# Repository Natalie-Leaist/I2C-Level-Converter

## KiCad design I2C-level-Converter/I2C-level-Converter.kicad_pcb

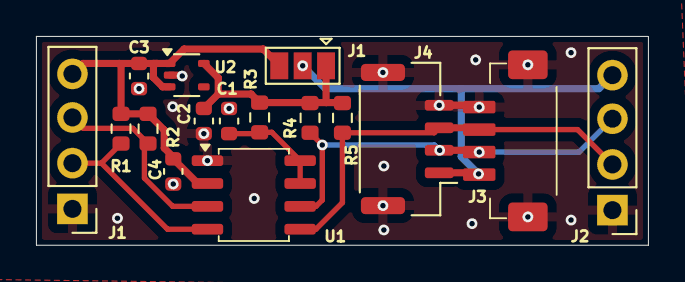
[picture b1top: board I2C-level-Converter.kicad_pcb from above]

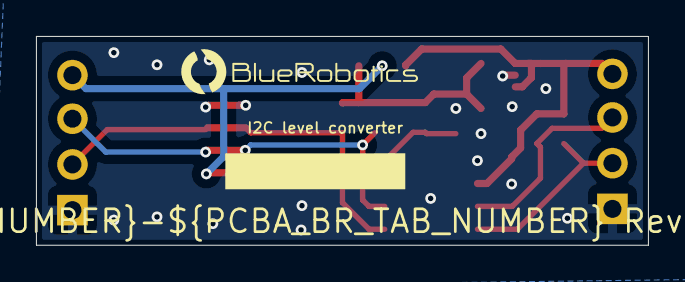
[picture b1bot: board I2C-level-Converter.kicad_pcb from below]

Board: 2 copper layers, 34.0 x 11.6 mm, 18 parts (2 on the bottom side), 9 nets.

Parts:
C1, C4: 100nF 100V; C_0603_1608Metric-minimized
C2, C3: 1uF 50V; C_0603_1608Metric-minimized
GL1: JLC_Number
GL2: BR_Logo
J1: Pin_Header_1x4_2.54mm_Vertical
J1#2: Solder_Jumper_3_Bridged12_flipped; SolderJumper-3_P1.3mm_Open_Pad1.0x1.5mm_paste
J2: 4-pin header; Pin_Header_1x4_2.54mm_Vertical
J3: DF13-4P-1.25V(21); HRS_DF13C_4P_1.25V(21)
J4: 4-pin GH; BM04B-GHS-TBT
R1, R2, R4, R5: 1k; R_0603_1608Metric
R3: 200k; R_0603_1608Metric
U1: PCA9306D,118; SO-8_3.9x4.9mm_P1.27mm_correct
U2: MIC5365-3.3YC5; SOT-353_SC-70-5

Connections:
3.3V: C2.1, J1#2.1 (B), R3.1, R4.1, R5.1, U2.5 (VOUT)
5V: C3.1, C4.1, J1.4, J1#2.3 (A), R1.1, R2.1, U1.2 (VREF1), U2.1 (VIN), U2.3 (EN)
/SCL1: J1.3, R2.2, U1.3 (SCL1)
/SCL2: J2.3, J3.2 (Pin_A2), J4.2, R4.2, U1.6 (SCL2)
/SDA1: J1.2, R1.2, U1.4 (SDA1)
/SDA2: J2.2, J3.3 (Pin_A3), J4.3, R5.2, U1.5 (SDA2)
GND: C1.2, C2.2, C3.2, C4.2, J1.1, J2.1, J3.4 (Pin_A4), J3.MP, J4.4, J4.MP, U1.1 (GND), U2.2 (GND)
unnamed: C1.1, R3.2, U1.7 (VREF2), U1.8 (EN)
V_DEVICE: J1#2.2 (C), J2.4, J3.1 (Pin_A1), J4.1

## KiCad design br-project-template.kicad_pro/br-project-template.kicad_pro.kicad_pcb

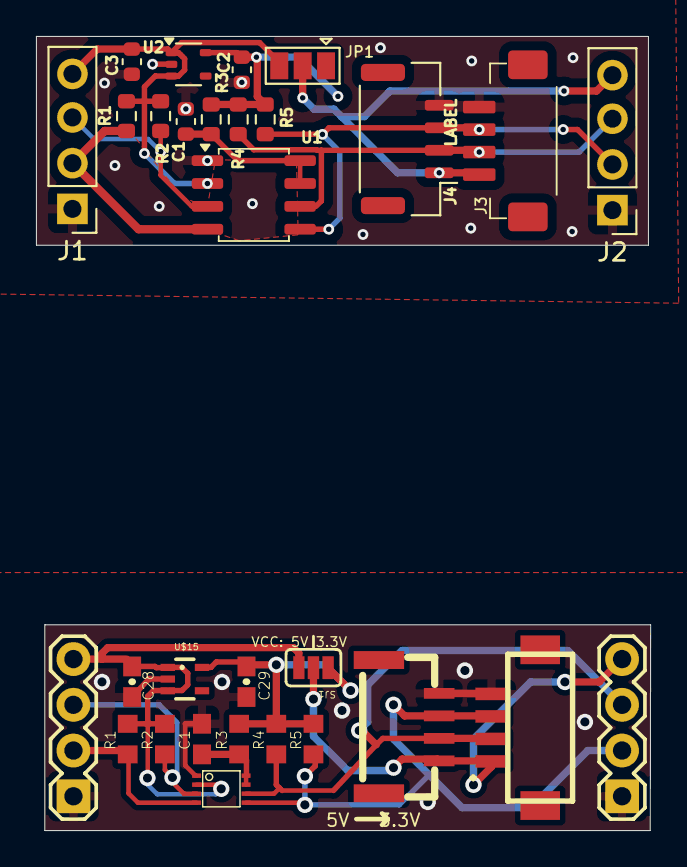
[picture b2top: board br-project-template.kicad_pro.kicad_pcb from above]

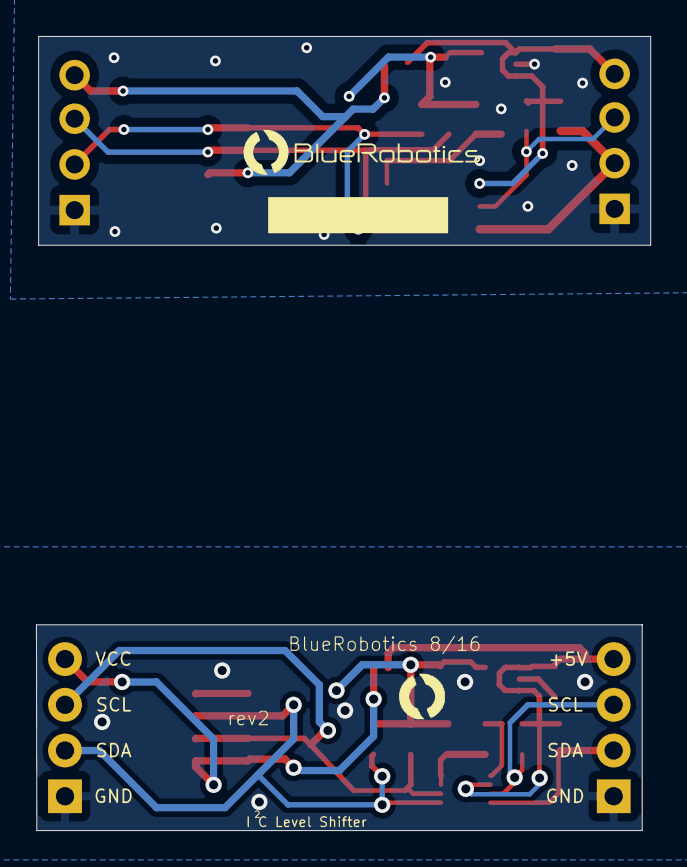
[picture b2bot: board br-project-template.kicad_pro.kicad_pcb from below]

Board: 2 copper layers, 34.1 x 44.1 mm, 33 parts (3 on the bottom side), 17 nets.

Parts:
C1: 0.1uF; C0603
C1#2: 10nF 100V; C_0603_1608Metric-minimized
C2, C3: 1uF 50V; C_0603_1608Metric-minimized
C28, C29: 1uF; 0603-CAP
GL101: JLC_Number
GL102: BR_Logo
J1, J2: Pin_Header_1x4_2.54mm_Vertical
J3: DF13-4P-1.25V(21); HRS_DF13C_4P_1.25V(21)
J4: LABEL; BM04B-GHS-TBT
JP1, JP2: 1X04
JP1#2: Solder_Jumper_3_Bridged12; SolderJumper-3_P1.3mm_Open_Pad1.0x1.5mm
R1, R2, R4#2, R5: 1k; R_0603_1608Metric
R1#2, R2#2, R4, R5#2: 1K; R0603
R3: 200K; R0603
R3#2: 200k; R_0603_1608Metric
SJ1: PAD-JUMPER-3-2OF3_NC_BY_PASTE_YES_SILK_FULL_BOX
U1: PCA9306DC1; PSOP-8
U1#2: PCA9306D,118; SO-8_3.9x4.9mm_P1.27mm_correct
U2: MIC5365-3.3YC5; SOT-353_SC-70-5
U$1: DF13-4P-1.25V; DF13C-4P-1.25V
U$2: JST-GH-4SMT; JST-GH-TOP-4
U$3: LOGOBR-LOGO-S; BR-LOGO-SMALL
U$15: VREG-MIC5365; SC70-5L

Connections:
+3.3V: C29.1, R3.2, R4.2, R5#2.2, SJ1.1, U$15.5
+5V: C28.1, JP1.4, R1#2.2, R2#2.2, SJ1.3, U1.2, U$15.1, U$15.3
/+3.3V: C2.1, JP1#2.1 (A), R3#2.1, R4#2.1, R5.1, U2.5 (VOUT)
/+5V: C3.1, J1.4, JP1#2.3 (B), R1.1, R2.1, U1#2.2 (VREF1), U2.1 (VIN), U2.3 (EN)
/SCL1: J1.3, R2.2, U1#2.3 (SCL1)
/SCL2: J2.3, J3.2 (Pin_A2), J4.2, R4#2.2, U1#2.6 (SCL2)
/SDA1: J1.2, R1.2, U1#2.4 (SDA1)
/SDA2: J2.2, J3.3 (Pin_A3), J4.3, R5.2, U1#2.5 (SDA2)
/V_DEVICE: J2.4, J3.1 (Pin_A1), J4.1, JP1#2.2 (C)
GND: C1.2, C1#2.2, C2.2, C3.2, C28.2, C29.2, J1.1, J2.1, J3.4 (Pin_A4), J4.4, JP1.1, JP2.1, U1.1, U1#2.1 (GND), U2.2 (GND), U$1.P$4, U$2.4, U$15.2
unnamed: C1.1, R3.1, U1.7, U1.8
unnamed: C1#2.1, R3#2.2, U1#2.7 (VREF2), U1#2.8 (EN)
SCL1: JP1.3, R2#2.1, U1.3
SCL2: JP2.3, R4.1, U1.6, U$1.P$2, U$2.2
SDA1: JP1.2, R1#2.1, U1.4
SDA2: JP2.2, R5#2.1, U1.5, U$1.P$3, U$2.3
V_DEVICE: JP2.4, SJ1.2, U$1.P$1, U$2.1

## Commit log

2026-01-08 almost finish board
2026-01-10 finish pcb (mostly)
2026-01-24 finish
